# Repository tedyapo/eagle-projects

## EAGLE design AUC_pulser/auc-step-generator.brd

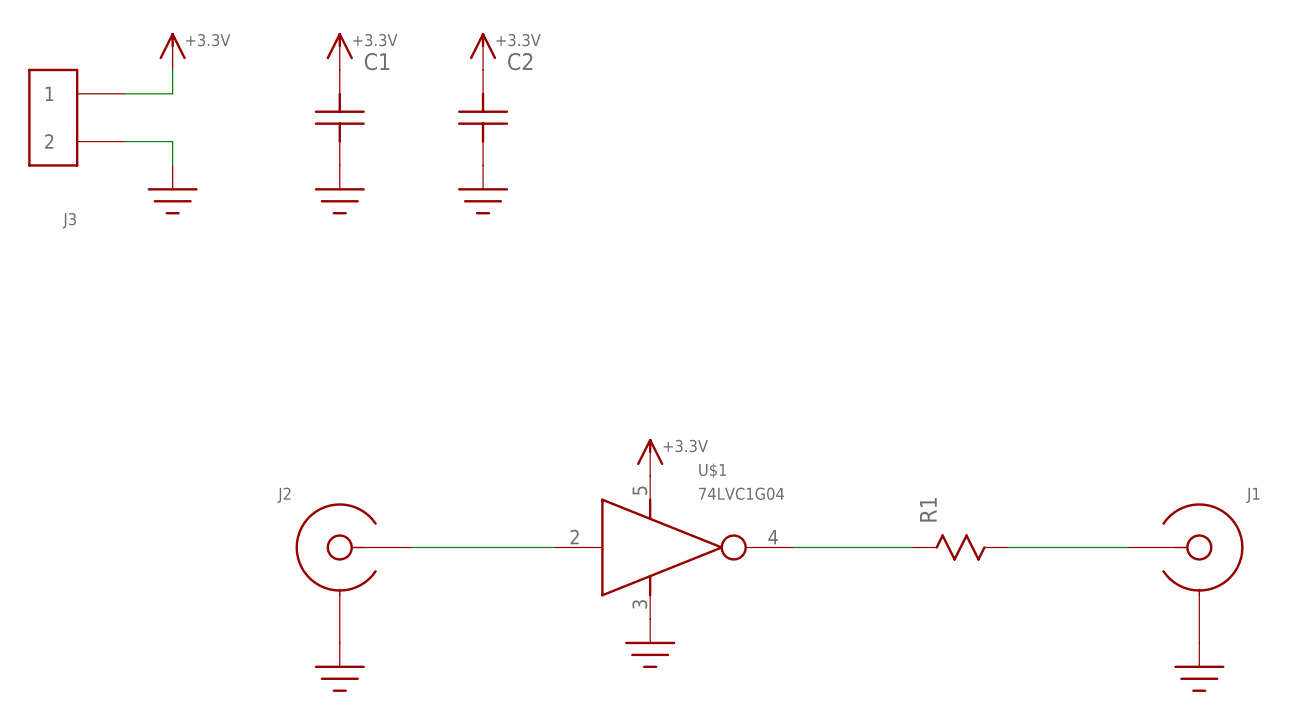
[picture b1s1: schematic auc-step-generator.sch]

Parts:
C1: C1206; 1206
C2: C0603
J1, J2: SMA-EDGE-LAUNCH4020_TAPER; SMA_EDGE_LAUNCH_2L_4020_TAPER
J3: HEADER_2PIN
R1: R0603
U$1: 74LVC1G04; SOT23-5

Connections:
+3.3V: C1.P$2, C2.P$2, J3.1, U$1.5 (VCC)
GND: C1.P$1, C2.P$1, J1.BOTTOM_GND (SHIELD), J1.GND@1 (SHIELD), J1.GND@2 (SHIELD), J1.GND@3 (SHIELD), J1.GND@4 (SHIELD), J1.GND@5 (SHIELD), J1.GND@6 (SHIELD), J1.GND@7 (SHIELD), J1.GND@8 (SHIELD), J1.GND@14 (SHIELD), J1.GND@15 (SHIELD), J1.GND@16 (SHIELD), J1.GND@17 (SHIELD), J1.GND_PAD1 (SHIELD), J1.GND_PAD2 (SHIELD), J1.P$1 (SHIELD), J1.P$2 (SHIELD), J2.BOTTOM_GND (SHIELD), J2.GND@1 (SHIELD), J2.GND@2 (SHIELD), J2.GND@3 (SHIELD), J2.GND@4 (SHIELD), J2.GND@5 (SHIELD), J2.GND@6 (SHIELD), J2.GND@7 (SHIELD), J2.GND@8 (SHIELD), J2.GND@14 (SHIELD), J2.GND@15 (SHIELD), J2.GND@16 (SHIELD), J2.GND@17 (SHIELD), J2.GND_PAD1 (SHIELD), J2.GND_PAD2 (SHIELD), J2.P$1 (SHIELD), J2.P$2 (SHIELD), J3.2, U$1.3 (GND)
unnamed: J2.CENTER@1 (CENTER), U$1.2 (IN)
unnamed: R1.P$1, U$1.4 (OUT)
unnamed: J1.CENTER@1 (CENTER), R1.P$2

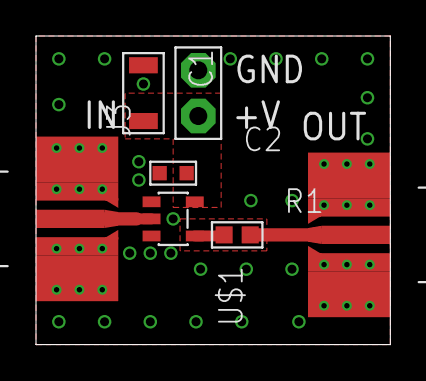
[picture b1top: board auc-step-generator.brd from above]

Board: 2 copper layers, 19.7 x 17.1 mm, 7 parts (0 on the bottom side), 5 nets.

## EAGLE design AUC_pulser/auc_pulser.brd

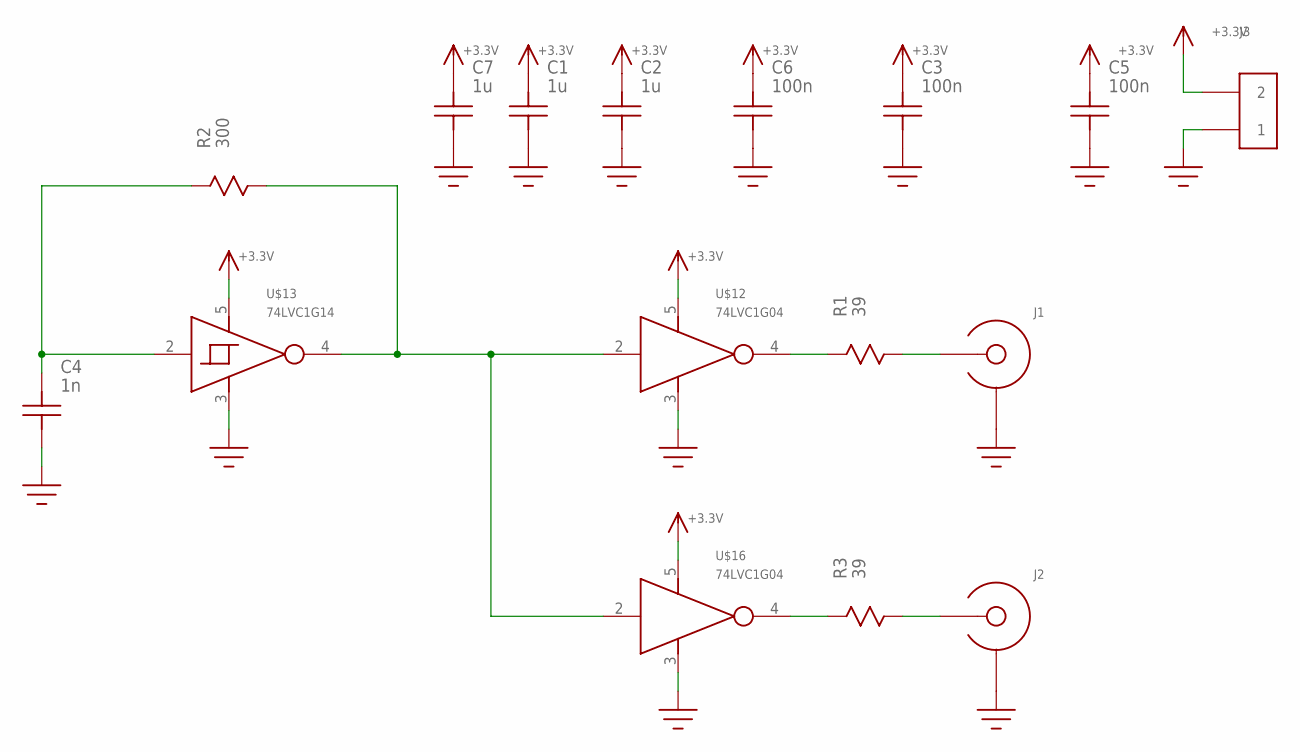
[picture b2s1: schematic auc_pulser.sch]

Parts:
C1, C2, C7: 1u; 0805
C3, C5, C6: 100n; C0603
C4: 1n; C0603
J1: BNC_MALE_PCB
J2: EDGE_LAUNCH_JACK; EDGE_LAUNCH_RF_CON
J3: HEADER_2PIN
R1, R3: 39; R0603
R2: 300; R0603
U$12, U$16: 74LVC1G04; SOT23-5
U$13: 74LVC1G14; SOT23-5

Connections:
+3.3V: C1.P$2, C2.P$2, C3.P$2, C5.P$2, C6.P$2, C7.P$2, J3.2, U$12.5 (VCC), U$13.5 (VCC), U$16.5 (VCC)
GND: C1.P$1, C2.P$1, C3.P$1, C4.P$1, C5.P$1, C6.P$1, C7.P$1, J1.SHIELD@1 (SHIELD), J1.SHIELD@2 (SHIELD), J1.SHIELD@3 (SHIELD), J1.SHIELD@4 (SHIELD), J2.GND@1 (SHIELD), J2.GND@2 (SHIELD), J2.GND@3 (SHIELD), J2.GND@4 (SHIELD), J2.GND@5 (SHIELD), J2.GND@6 (SHIELD), J2.GND@7 (SHIELD), J2.GND@8 (SHIELD), J2.GND@9 (SHIELD), J2.GND@10 (SHIELD), J2.GND@11 (SHIELD), J2.GND@12 (SHIELD), J2.SHIELD@1 (SHIELD), J2.SHIELD@2 (SHIELD), J3.1, U$12.3 (GND), U$13.3 (GND), U$16.3 (GND)
unnamed: J1.CENTER, R1.P$2
unnamed: R1.P$1, U$12.4 (OUT)
unnamed: C4.P$2, R2.P$1, U$13.2 (IN)
unnamed: R2.P$2, U$12.2 (IN), U$13.4 (OUT), U$16.2 (IN)
unnamed: J2.CENTER, R3.P$2
unnamed: R3.P$1, U$16.4 (OUT)

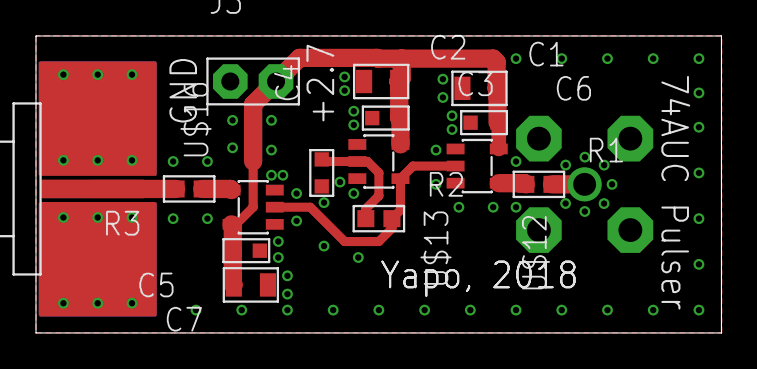
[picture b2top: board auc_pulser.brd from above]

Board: 2 copper layers, 38.1 x 16.5 mm, 16 parts (0 on the bottom side), 8 nets.

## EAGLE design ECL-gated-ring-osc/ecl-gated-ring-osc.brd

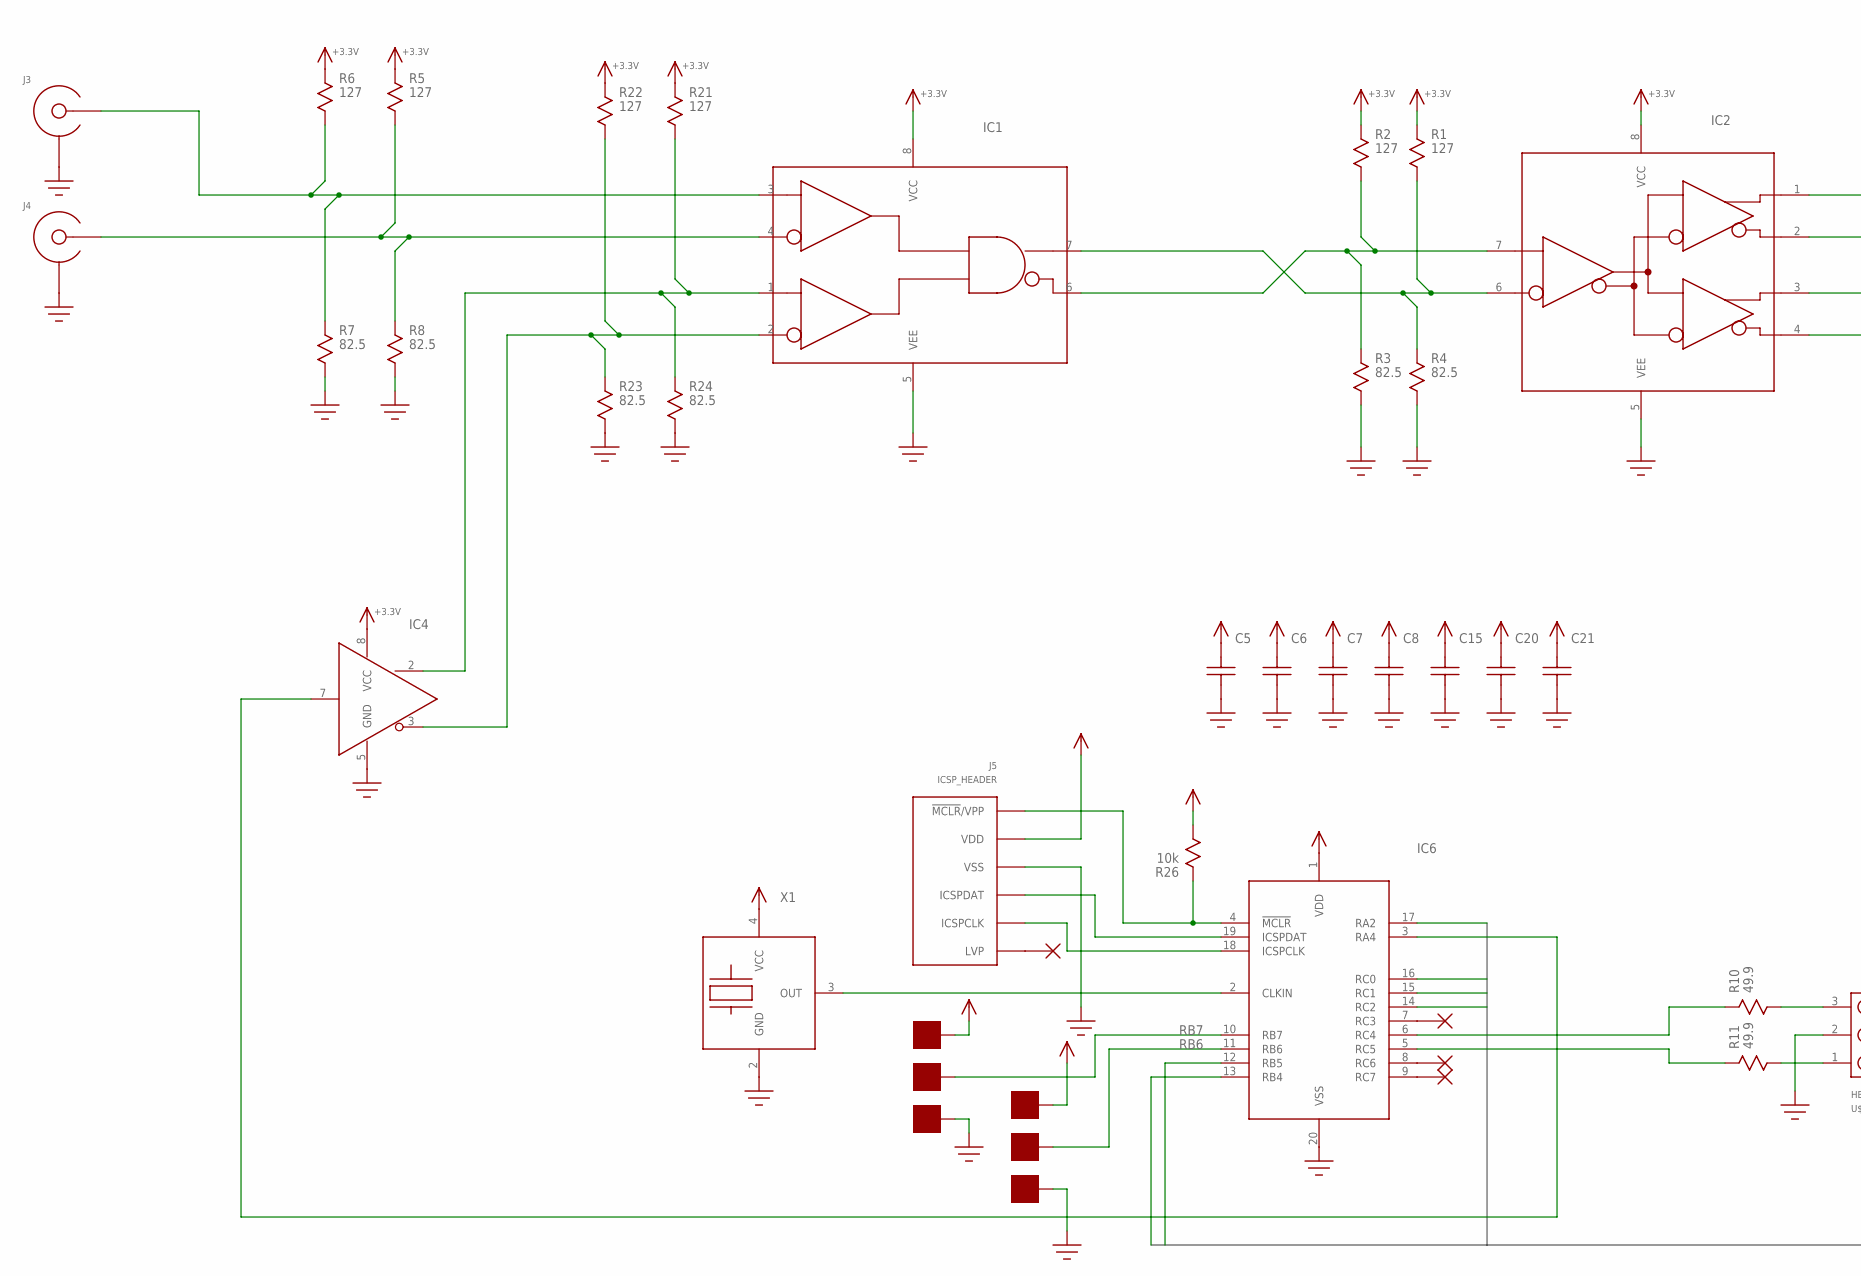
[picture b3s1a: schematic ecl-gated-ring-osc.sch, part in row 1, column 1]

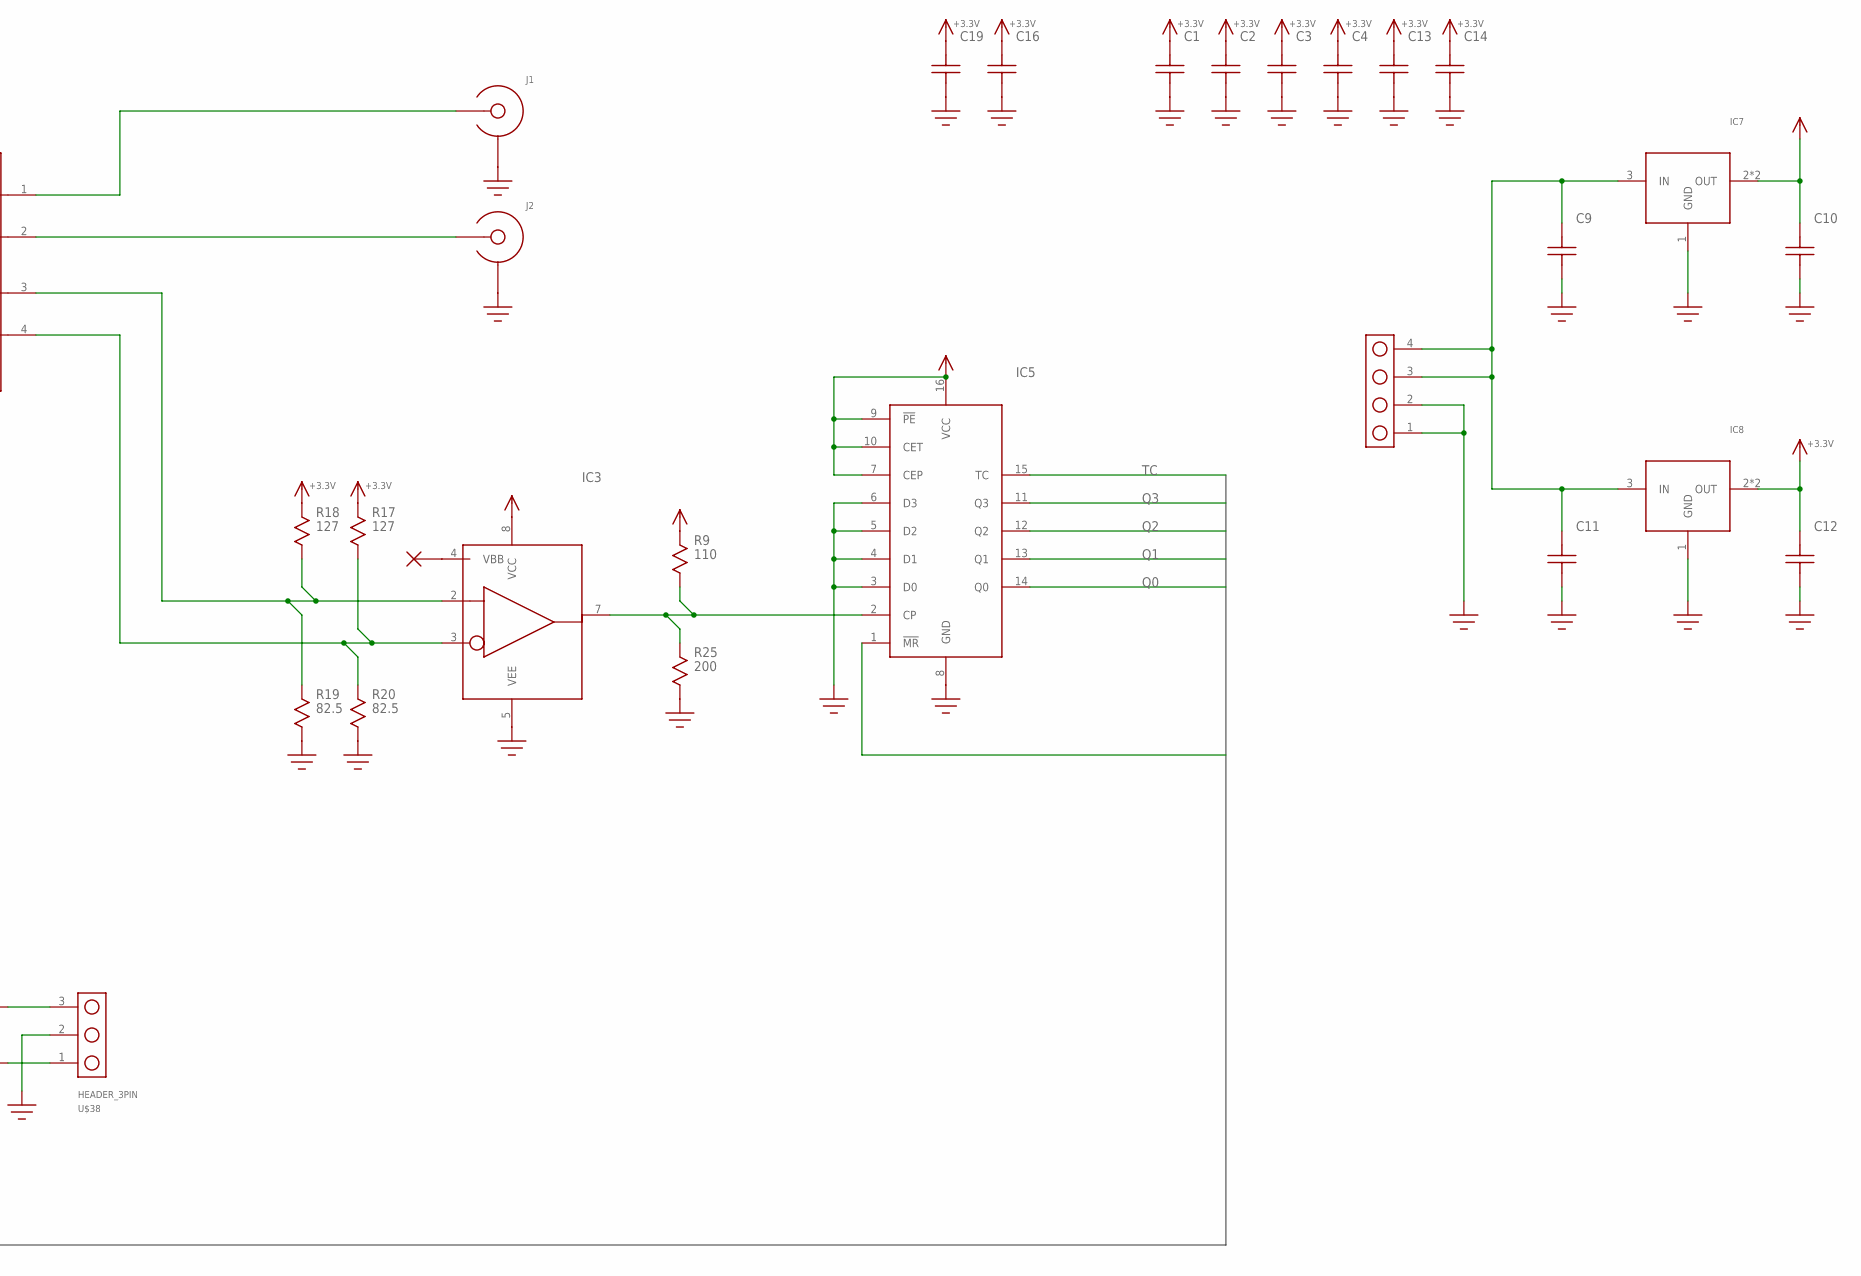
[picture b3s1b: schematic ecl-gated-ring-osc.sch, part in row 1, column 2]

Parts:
C1, C2, C3, C4, C5, C6, C7, C8, C13, C14, C15, C16, C19, C20, C21: C0603
C9, C10, C11, C12: C1206; 1206
IC1: SY10EP05V; SOIC8
IC2: SY10EP11U; SOIC8
IC3: MC100EPT21; SOIC8
IC4: MC100LVELT20; SOIC8
IC5: 74XX161; SOIC-16
IC6: PIC16F15345; SOIC-20N
IC7, IC8: AZ1117E; SOT-223
J1, J2, J3, J4: SMA-EDGE-LAUNCH4L-4020-TAPER-FIXED; SMA_EDGE_LAUNCH_4L_4020_TAPER_FIXED
J5: ICSP_HEADER; HEADER_6PIN
J6: HEADER_4PIN
R1, R2, R5, R6, R17, R18, R21, R22: 127; R0603
R3, R4, R7, R8, R19, R20, R23, R24: 82.5; R0603
R9: 110; R0603
R10, R11: 49.9; R0603
R25: 200; R0603
R26: 10k; R0603
U$38: HEADER_3PIN
U$73, U$74, U$75, U$83, U$84, U$92: PAD50MIL; PAD_50MIL
X1: XTAL_OSC; XTAL_3.2X5

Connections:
!MR!: IC5.1 (!MR!), IC6.12 (RB5)
+3.3V: C1.P$2, C2.P$2, C3.P$2, C4.P$2, C12.P$2, C13.P$2, C14.P$2, C16.P$2, C19.P$2, IC1.8 (VCC), IC2.8 (VCC), IC4.8 (VCC), IC8.2 (OUT), IC8.4 (OUT), R1.P$1, R2.P$1, R5.P$1, R6.P$1, R17.P$1, R18.P$1, R21.P$1, R22.P$1
GND: C1.P$1, C2.P$1, C3.P$1, C4.P$1, C5.P$1, C6.P$1, C7.P$1, C8.P$1, C9.P$1, C10.P$1, C11.P$1, C12.P$1, C13.P$1, C14.P$1, C15.P$1, C16.P$1, C19.P$1, C20.P$1, C21.P$1, IC1.5 (VEE), IC2.5 (VEE), IC3.5 (VEE), IC4.5 (GND), IC5.3 (D0), IC5.4 (D1), IC5.5 (D2), IC5.6 (D3), IC5.8 (GND), IC6.20 (VSS), IC7.1 (GND), IC8.1 (GND), J1.BOTTOM_GND (SHIELD), J1.GND@1 (SHIELD), J1.GND@2 (SHIELD), J1.GND@3 (SHIELD), J1.GND@4 (SHIELD), J1.GND@5 (SHIELD), J1.GND@6 (SHIELD), J1.GND@7 (SHIELD), J1.GND@8 (SHIELD), J1.GND@14 (SHIELD), J1.GND@15 (SHIELD), J1.GND@16 (SHIELD), J1.GND@17 (SHIELD), J1.GND_PAD1 (SHIELD), J1.GND_PAD2 (SHIELD), J1.P$1 (SHIELD), J1.P$2 (SHIELD), J2.BOTTOM_GND (SHIELD), J2.GND@1 (SHIELD), J2.GND@2 (SHIELD), J2.GND@3 (SHIELD), J2.GND@4 (SHIELD), J2.GND@5 (SHIELD), J2.GND@6 (SHIELD), J2.GND@7 (SHIELD), J2.GND@8 (SHIELD), J2.GND@14 (SHIELD), J2.GND@15 (SHIELD), J2.GND@16 (SHIELD), J2.GND@17 (SHIELD), J2.GND_PAD1 (SHIELD), J2.GND_PAD2 (SHIELD), J2.P$1 (SHIELD), J2.P$2 (SHIELD), J3.BOTTOM_GND (SHIELD), J3.GND@1 (SHIELD), J3.GND@2 (SHIELD), J3.GND@3 (SHIELD), J3.GND@4 (SHIELD), J3.GND@5 (SHIELD), J3.GND@6 (SHIELD), J3.GND@7 (SHIELD), J3.GND@8 (SHIELD), J3.GND@14 (SHIELD), J3.GND@15 (SHIELD), J3.GND@16 (SHIELD), J3.GND@17 (SHIELD), J3.GND_PAD1 (SHIELD), J3.GND_PAD2 (SHIELD), J3.P$1 (SHIELD), J3.P$2 (SHIELD), J4.BOTTOM_GND (SHIELD), J4.GND@1 (SHIELD), J4.GND@2 (SHIELD), J4.GND@3 (SHIELD), J4.GND@4 (SHIELD), J4.GND@5 (SHIELD), J4.GND@6 (SHIELD), J4.GND@7 (SHIELD), J4.GND@8 (SHIELD), J4.GND@14 (SHIELD), J4.GND@15 (SHIELD), J4.GND@16 (SHIELD), J4.GND@17 (SHIELD), J4.GND_PAD1 (SHIELD), J4.GND_PAD2 (SHIELD), J4.P$1 (SHIELD), J4.P$2 (SHIELD), J5.3 (VSS), J6.1, J6.2, R3.P$2, R4.P$2, R7.P$2, R8.P$2, R19.P$2, R20.P$2, R23.P$2, R24.P$2, R25.P$2, U$38.2, U$83.P$1, U$92.P$1, X1.2 (GND)
unnamed: IC2.3 (Q1), IC3.2 (D), R18.P$2, R19.P$1
unnamed: IC1.6 (!Q!), IC2.7 (D), R2.P$2, R3.P$1
unnamed: IC1.4 (!D1!), J4.CENTER@1 (CENTER), J4.P$3 (CENTER), R5.P$2, R8.P$1
unnamed: IC1.3 (D1), J3.CENTER@1 (CENTER), J3.P$3 (CENTER), R6.P$2, R7.P$1
unnamed: IC1.7 (Q), IC2.6 (!D!), R1.P$2, R4.P$1
unnamed: IC2.2 (!Q0!), J2.CENTER@1 (CENTER), J2.P$3 (CENTER)
unnamed: IC2.1 (Q0), J1.CENTER@1 (CENTER), J1.P$3 (CENTER)
unnamed: IC2.4 (!Q1!), IC3.3 (!D!), R17.P$2, R20.P$1
unnamed: IC1.1 (D0), IC4.2 (Q), R21.P$2, R24.P$1
unnamed: IC1.2 (!D0!), IC4.3 (!Q!), R22.P$2, R23.P$1
unnamed: IC3.7 (Q), IC5.2 (CP), R9.P$2, R25.P$1
unnamed: IC6.4 (!MCLR!), J5.1 (!MCLR!/VPP), R26.P$1
unnamed: IC6.19 (ICSPDAT), J5.4 (ICSPDAT)
unnamed: IC6.18 (ICSPCLK), J5.5 (ICSPCLK)
unnamed: IC6.2 (CLKIN), X1.3 (OUT)
unnamed: R10.P$2, U$38.3
unnamed: R11.P$2, U$38.1
unnamed: IC6.6 (RC4), R10.P$1
unnamed: IC6.5 (RC5), R11.P$1
unnamed: C9.P$2, C11.P$2, IC7.3 (IN), IC8.3 (IN), J6.3, J6.4
unnamed: IC4.7 (D), IC6.3 (RA4)
Q0: IC5.14 (Q0), IC6.14 (RC2)
Q1: IC5.13 (Q1), IC6.15 (RC1)
Q2: IC5.12 (Q2), IC6.16 (RC0)
Q3: IC5.11 (Q3), IC6.17 (RA2)
RB6: IC6.11 (RB6), U$74.P$1
RB7: IC6.10 (RB7), U$73.P$1
TC: IC5.15 (TC), IC6.13 (RB4)
VCC2: C5.P$2, C6.P$2, C7.P$2, C8.P$2, C10.P$2, C15.P$2, C20.P$2, C21.P$2, IC3.8 (VCC), IC5.7 (CEP), IC5.9 (!PE!), IC5.10 (CET), IC5.16 (VCC), IC6.1 (VDD), IC7.2 (OUT), IC7.4 (OUT), J5.2 (VDD), R9.P$1, R26.P$2, U$75.P$1, U$84.P$1, X1.4 (VCC)

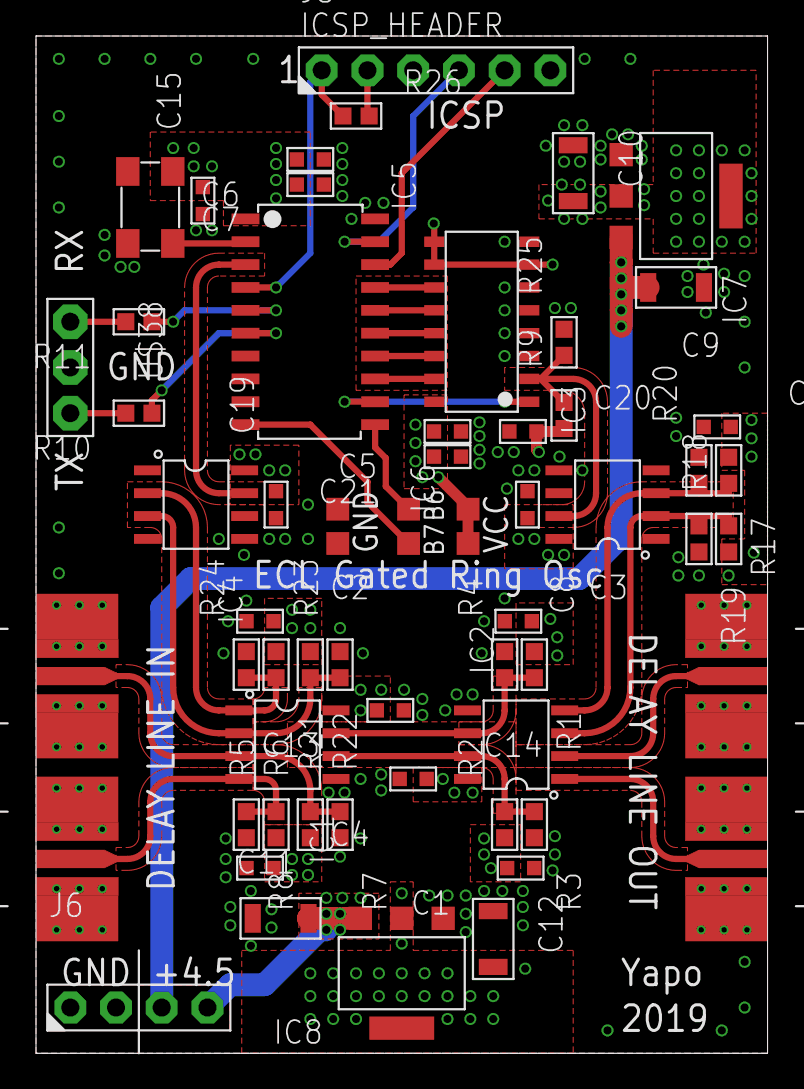
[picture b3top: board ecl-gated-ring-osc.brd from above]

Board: 4 copper layers, 40.6 x 56.5 mm, 62 parts (0 on the bottom side), 32 nets.

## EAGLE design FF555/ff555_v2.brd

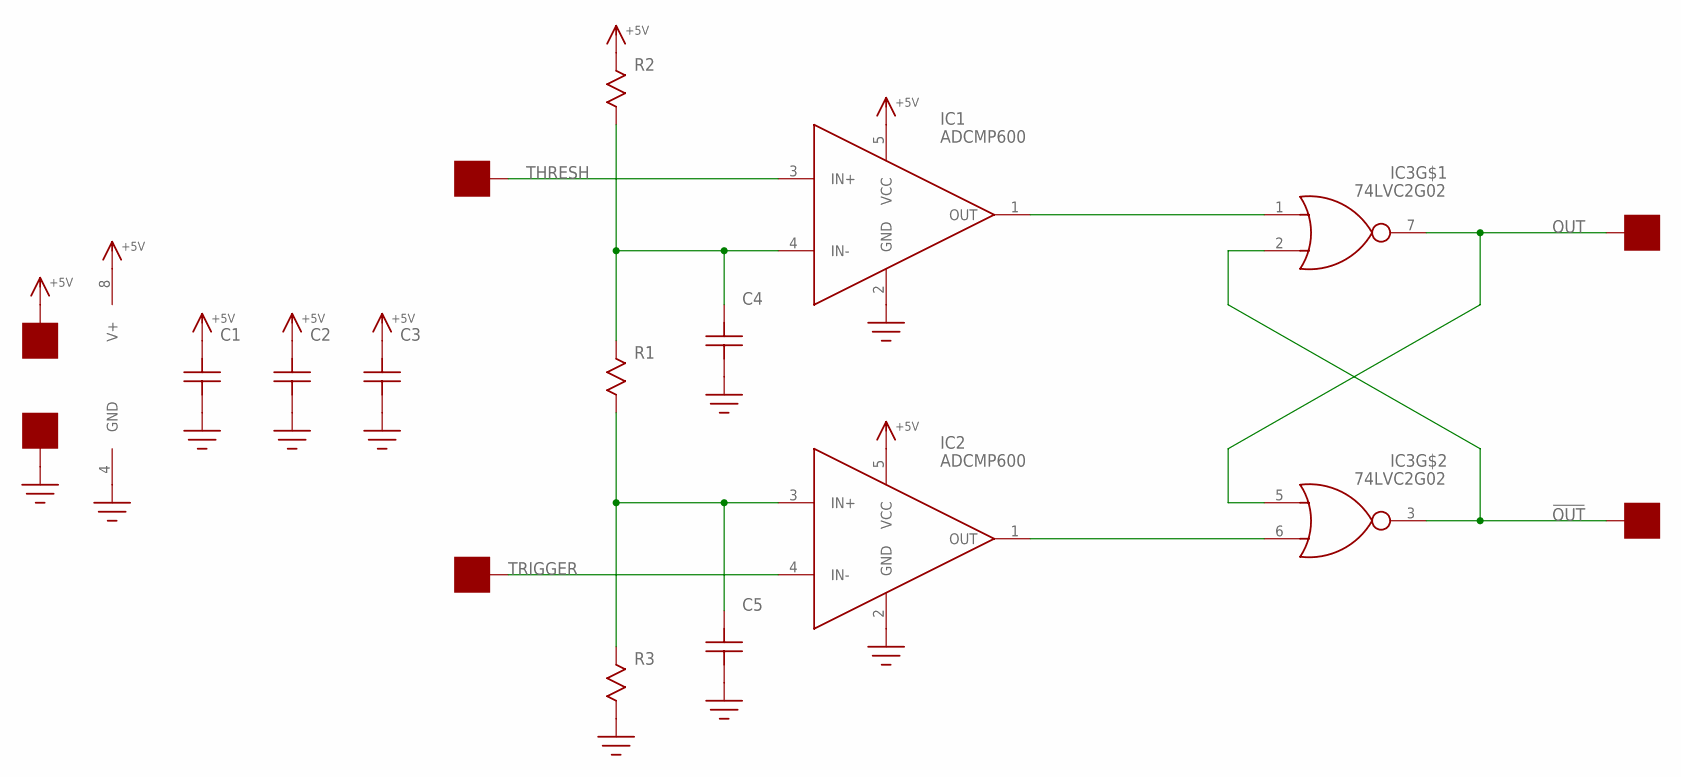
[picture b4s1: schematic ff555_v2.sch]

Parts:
C1, C2, C4, C5: C0603
C3: C0805; 0805
IC1, IC2: ADCMP600; SOT23-5
IC3: 74LVC2G02; TSSOP8
R1: R1206
R2, R3: R0603
U$15, U$16, U$17, U$18, U$19, U$20: PAD100MIL; PAD_100MIL

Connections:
!OUT!: IC3.2 (B), IC3.3 (Y), U$20.P$1
+5V: C1.P$2, C2.P$2, C3.P$2, IC1.5 (VCC), IC2.5 (VCC), IC3.8 (V+), R2.P$1, U$15.P$1
GND: C1.P$1, C2.P$1, C3.P$1, C4.P$1, C5.P$1, IC1.2 (GND), IC2.2 (GND), IC3.4 (GND), R3.P$2, U$16.P$1
unnamed: C4.P$2, IC1.4 (IN-), R1.P$1, R2.P$2
unnamed: C5.P$2, IC2.3 (IN+), R1.P$2, R3.P$1
unnamed: IC1.1 (OUT), IC3.1 (A)
unnamed: IC2.1 (OUT), IC3.6 (B)
OUT: IC3.5 (A), IC3.7 (Y), U$19.P$1
THRESH: IC1.3 (IN+), U$17.P$1
TRIGGER: IC2.4 (IN-), U$18.P$1

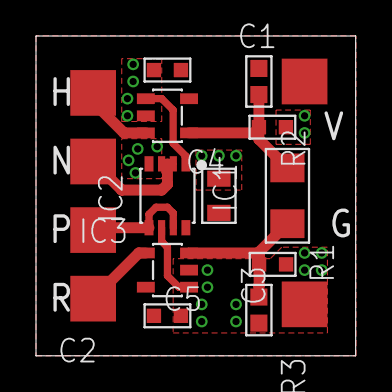
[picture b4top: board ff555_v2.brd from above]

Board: 2 copper layers, 17.8 x 17.8 mm, 17 parts (0 on the bottom side), 10 nets.

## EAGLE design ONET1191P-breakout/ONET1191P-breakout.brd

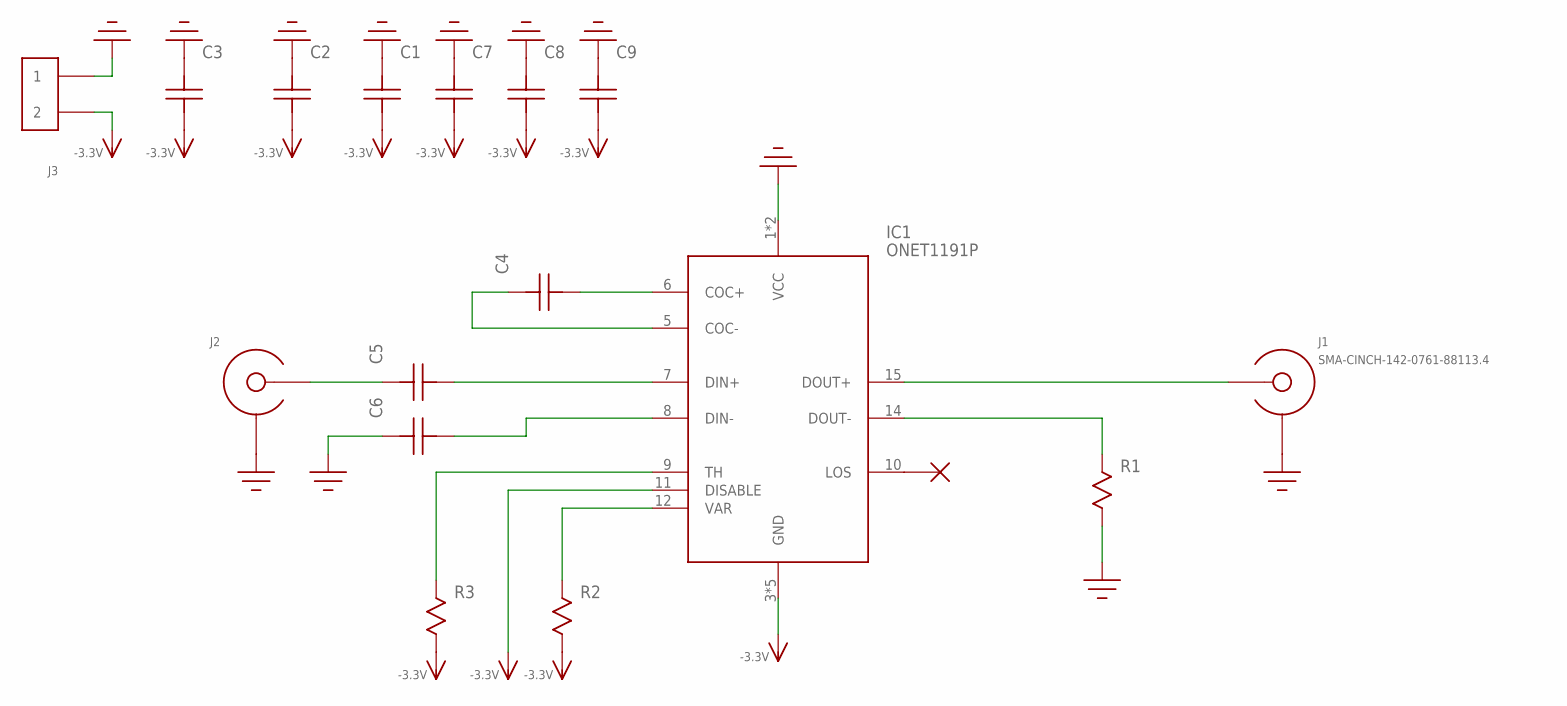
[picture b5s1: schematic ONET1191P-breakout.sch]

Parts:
C1, C2: C0603
C3: C1206; 1206
C4, C5, C6, C7, C8, C9: C; C0402
IC1: ONET1191P; TQFN16
J1: SMA-CINCH-142-0761-88113.4; SMA-CINCH-142-0761-881-13.4
J2: SMA-EDGE-LAUNCH4L-4020-TAPER-FIXED; SMA_EDGE_LAUNCH_4L_4020_TAPER_FIXED
J3: HEADER_2PIN
R1: R0402; 0402
R2, R3: R0603

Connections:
-3.3V: C1.P$1, C2.P$1, C3.P$1, C7.1, C8.1, C9.1, IC1.3 (GND), IC1.4 (GND), IC1.11 (DISABLE), IC1.13 (GND), IC1.16 (GND), IC1.EP (GND), J3.2, R2.P$2, R3.P$2
GND: C1.P$2, C2.P$2, C3.P$2, C6.2, C7.2, C8.2, C9.2, IC1.1 (VCC), IC1.2 (VCC), J1.GND@1 (SHIELD), J1.GND@2 (SHIELD), J1.GND@3 (SHIELD), J1.HOLE@1 (SHIELD), J1.HOLE@2 (SHIELD), J1.HOLE@3 (SHIELD), J1.HOLE@4 (SHIELD), J1.VIA@1 (SHIELD), J1.VIA@2 (SHIELD), J1.VIA@3 (SHIELD), J1.VIA@4 (SHIELD), J1.VIA@5 (SHIELD), J1.VIA@6 (SHIELD), J2.BOTTOM_GND (SHIELD), J2.GND@1 (SHIELD), J2.GND@2 (SHIELD), J2.GND@3 (SHIELD), J2.GND@4 (SHIELD), J2.GND@5 (SHIELD), J2.GND@6 (SHIELD), J2.GND@7 (SHIELD), J2.GND@8 (SHIELD), J2.GND@14 (SHIELD), J2.GND@15 (SHIELD), J2.GND@16 (SHIELD), J2.GND@17 (SHIELD), J2.GND_PAD1 (SHIELD), J2.GND_PAD2 (SHIELD), J2.P$1 (SHIELD), J2.P$2 (SHIELD), J3.1, R1.2
unnamed: C4.1, IC1.6 (COC+)
unnamed: C4.2, IC1.5 (COC-)
unnamed: IC1.14 (DOUT-), R1.1
unnamed: IC1.15 (DOUT+), J1.CENTER
unnamed: IC1.12 (VAR), R2.P$1
unnamed: IC1.9 (TH), R3.P$1
unnamed: C5.2, J2.CENTER@1 (CENTER), J2.P$3 (CENTER)
unnamed: C5.1, IC1.7 (DIN+)
unnamed: C6.1, IC1.8 (DIN-)

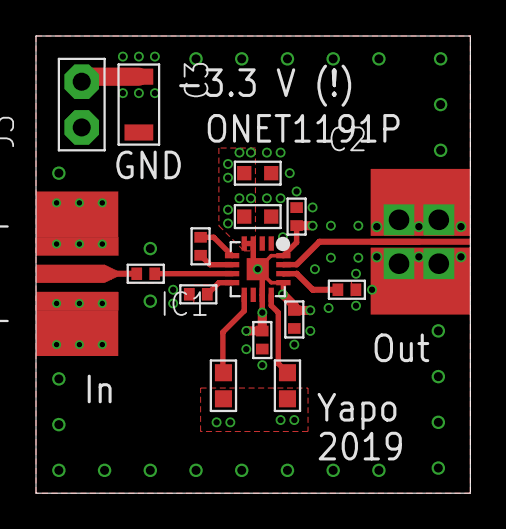
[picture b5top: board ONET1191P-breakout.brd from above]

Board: 4 copper layers, 24.1 x 25.4 mm, 16 parts (0 on the bottom side), 11 nets.

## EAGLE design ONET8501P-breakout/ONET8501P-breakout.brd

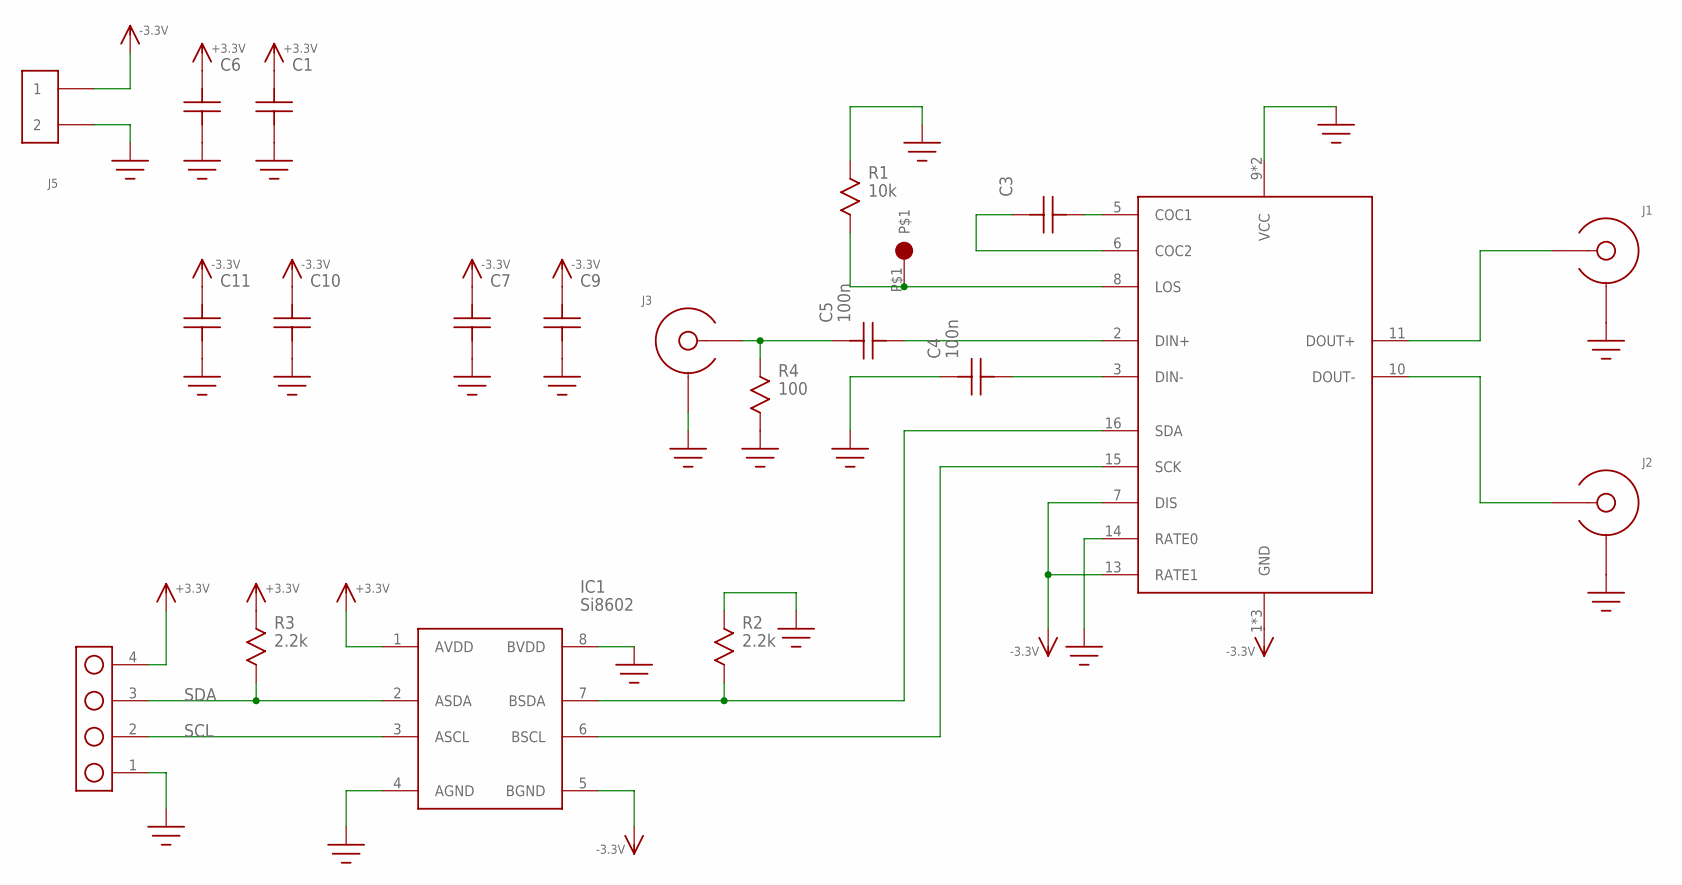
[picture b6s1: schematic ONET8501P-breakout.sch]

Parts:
C1, C3, C9, C10, C11: C0603
C4, C5: 100n; C0603
C6, C7: C1206; 1206
IC1: Si8602; SOIC8
IC2: ONET8501P; TQFN16-EP
J1, J2, J3: SMA-EDGE-LAUNCH4L_4035_TAPER; SMA_EDGE_LAUNCH_4L_4035_TAPER
J4: HEADER_4PIN
J5: HEADER_2PIN
P1: ICSP_PAD
R1: 10k; R0603
R2, R3: 2.2k; R0603
R4: 100; R0603

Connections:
+3.3V: C1.P$2, C6.P$2, IC1.1 (AVDD), J4.4, R3.P$1
-3.3V: C7.P$2, C9.P$2, C10.P$2, C11.P$2, IC1.5 (BGND), IC2.1 (GND), IC2.4 (GND), IC2.7 (DIS), IC2.13 (RATE1), IC2.EP (GND), J5.1
GND: C1.P$1, C4.P$2, C6.P$1, C7.P$1, C9.P$1, C10.P$1, C11.P$1, IC1.4 (AGND), IC1.8 (BVDD), IC2.9 (VCC), IC2.12 (VCC), IC2.14 (RATE0), J1.BOTTOM_GND (SHIELD), J1.GND@1 (SHIELD), J1.GND@2 (SHIELD), J1.GND@3 (SHIELD), J1.GND@4 (SHIELD), J1.GND@5 (SHIELD), J1.GND@6 (SHIELD), J1.GND@7 (SHIELD), J1.GND@8 (SHIELD), J1.GND@14 (SHIELD), J1.GND@15 (SHIELD), J1.GND@16 (SHIELD), J1.GND@17 (SHIELD), J1.GND_PAD1 (SHIELD), J1.GND_PAD2 (SHIELD), J1.P$1 (SHIELD), J1.P$2 (SHIELD), J2.BOTTOM_GND (SHIELD), J2.GND@1 (SHIELD), J2.GND@2 (SHIELD), J2.GND@3 (SHIELD), J2.GND@4 (SHIELD), J2.GND@5 (SHIELD), J2.GND@6 (SHIELD), J2.GND@7 (SHIELD), J2.GND@8 (SHIELD), J2.GND@14 (SHIELD), J2.GND@15 (SHIELD), J2.GND@16 (SHIELD), J2.GND@17 (SHIELD), J2.GND_PAD1 (SHIELD), J2.GND_PAD2 (SHIELD), J2.P$1 (SHIELD), J2.P$2 (SHIELD), J3.BOTTOM_GND (SHIELD), J3.GND@1 (SHIELD), J3.GND@2 (SHIELD), J3.GND@3 (SHIELD), J3.GND@4 (SHIELD), J3.GND@5 (SHIELD), J3.GND@6 (SHIELD), J3.GND@7 (SHIELD), J3.GND@8 (SHIELD), J3.GND@14 (SHIELD), J3.GND@15 (SHIELD), J3.GND@16 (SHIELD), J3.GND@17 (SHIELD), J3.GND_PAD1 (SHIELD), J3.GND_PAD2 (SHIELD), J3.P$1 (SHIELD), J3.P$2 (SHIELD), J4.1, J5.2, R1.P$1, R2.P$1, R4.P$2
unnamed: IC1.7 (BSDA), IC2.16 (SDA), R2.P$2
unnamed: IC1.6 (BSCL), IC2.15 (SCK)
unnamed: C3.P$1, IC2.5 (COC1)
unnamed: C3.P$2, IC2.6 (COC2)
unnamed: IC2.11 (DOUT+), J1.CENTER@1 (CENTER)
unnamed: IC2.10 (DOUT-), J2.CENTER@1 (CENTER)
unnamed: IC2.8 (LOS), P1.P$1, R1.P$2
unnamed: C4.P$1, IC2.3 (DIN-)
unnamed: C5.P$2, J3.CENTER@1 (CENTER), R4.P$1
unnamed: C5.P$1, IC2.2 (DIN+)
SCL: IC1.3 (ASCL), J4.2
SDA: IC1.2 (ASDA), J4.3, R3.P$2

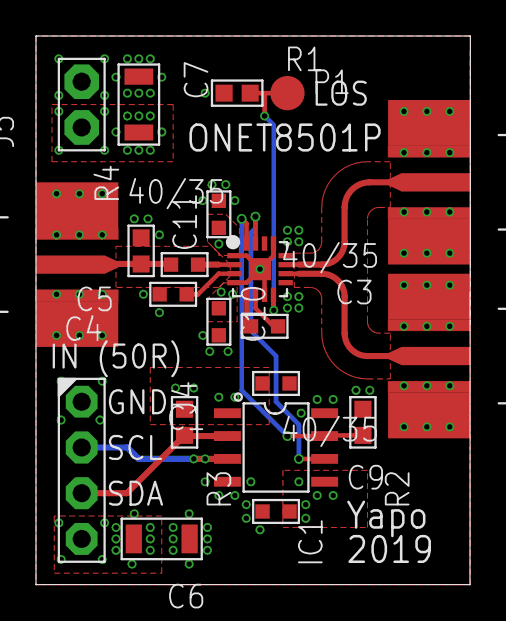
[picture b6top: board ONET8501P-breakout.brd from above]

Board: 4 copper layers, 24.1 x 30.5 mm, 21 parts (0 on the bottom side), 15 nets.

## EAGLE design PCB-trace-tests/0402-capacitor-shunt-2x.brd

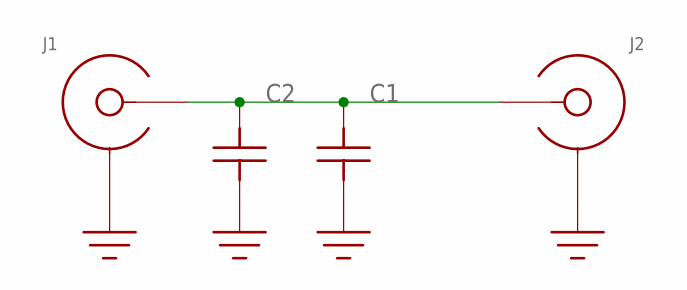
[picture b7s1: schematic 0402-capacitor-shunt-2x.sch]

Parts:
C1, C2: C; C0402
J1: SMA-EDGE-LAUNCH4020_TAPER; SMA_EDGE_LAUNCH_2L_4020_TAPER
J2: SMA-EDGE-LAUNCHCUT-PIN; SMA_EDGE_LAUNCH_2L_4020_CUT_PIN

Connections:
GND: C1.1, C2.1, J1.BOTTOM_GND (SHIELD), J1.GND@1 (SHIELD), J1.GND@2 (SHIELD), J1.GND@3 (SHIELD), J1.GND@4 (SHIELD), J1.GND@5 (SHIELD), J1.GND@6 (SHIELD), J1.GND@7 (SHIELD), J1.GND@8 (SHIELD), J1.GND@14 (SHIELD), J1.GND@15 (SHIELD), J1.GND@16 (SHIELD), J1.GND@17 (SHIELD), J1.GND_PAD1 (SHIELD), J1.GND_PAD2 (SHIELD), J1.P$1 (SHIELD), J1.P$2 (SHIELD), J2.BOTTOM_GND (SHIELD), J2.GND@1 (SHIELD), J2.GND@2 (SHIELD), J2.GND@3 (SHIELD), J2.GND@4 (SHIELD), J2.GND@5 (SHIELD), J2.GND@6 (SHIELD), J2.GND@7 (SHIELD), J2.GND@8 (SHIELD), J2.GND@14 (SHIELD), J2.GND@15 (SHIELD), J2.GND@16 (SHIELD), J2.GND@17 (SHIELD), J2.GND_PAD1 (SHIELD), J2.GND_PAD2 (SHIELD)
unnamed: C1.2, C2.2, J1.CENTER@1 (CENTER), J2.CENTER@1 (CENTER), J2.CENTER@3 (CENTER)

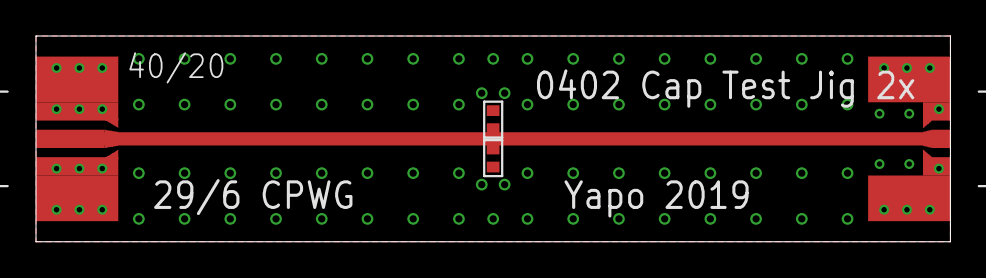
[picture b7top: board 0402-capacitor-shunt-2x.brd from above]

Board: 2 copper layers, 50.8 x 11.4 mm, 4 parts (0 on the bottom side), 2 nets.

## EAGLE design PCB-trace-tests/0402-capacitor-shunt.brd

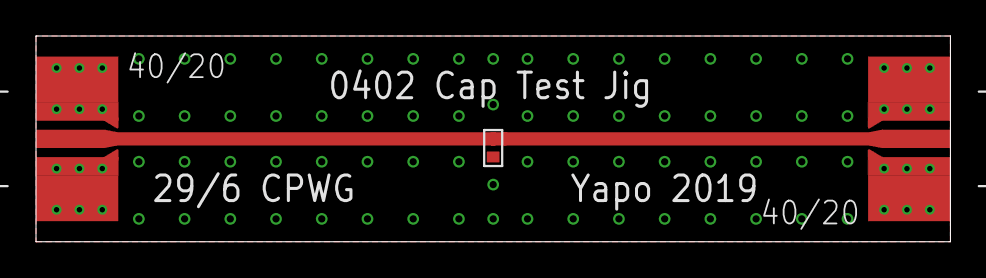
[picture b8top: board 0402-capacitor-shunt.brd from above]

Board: 2 copper layers, 50.8 x 11.4 mm, 3 parts (0 on the bottom side), 2 nets.

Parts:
C1: C0402
J1, J2: SMA_EDGE_LAUNCH_2L_4020_TAPER

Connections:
GND: C1.1, J1.BOTTOM_GND, J1.GND@1, J1.GND@2, J1.GND@3, J1.GND@4, J1.GND@5, J1.GND@6, J1.GND@7, J1.GND@8, J1.GND@14, J1.GND@15, J1.GND@16, J1.GND@17, J1.GND_PAD1, J1.GND_PAD2, J1.P$1, J1.P$2, J2.BOTTOM_GND, J2.GND@1, J2.GND@2, J2.GND@3, J2.GND@4, J2.GND@5, J2.GND@6, J2.GND@7, J2.GND@8, J2.GND@14, J2.GND@15, J2.GND@16, J2.GND@17, J2.GND_PAD1, J2.GND_PAD2, J2.P$1, J2.P$2
unnamed: C1.2, J1.CENTER@1, J2.CENTER@1
